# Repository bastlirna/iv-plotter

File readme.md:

# I·V Plotter 

_Tiny application for measurement of IV characteristics via DPS 5005 digital power supply._

## How it works

Some of [Rui Deng](https://rdtech.aliexpress.com) digital power supplies e.g. [DPS 5005](https://www.aliexpress.com/item/1000004290003.html) can be controled from PC via USB convertor. There is oficial app, but more importnat API documentation. So why not to use this API for something interesting that official app can not do...

### Resolution

DPS has resolution 10 mV for voltage and 1 mA for current. Also change of output is very slow and one must wait for settle down. 

This application is there for more demo or tool for explaining what is IV curve for newbes more then serious tool.

> Hovewer it can be used as example how to control DPS via API.

## How to use

```
git clone git@github.com:bastlirna/iv-plotter.git
cd app
npm install
npm start ttyUSB0
```

And enjoy...

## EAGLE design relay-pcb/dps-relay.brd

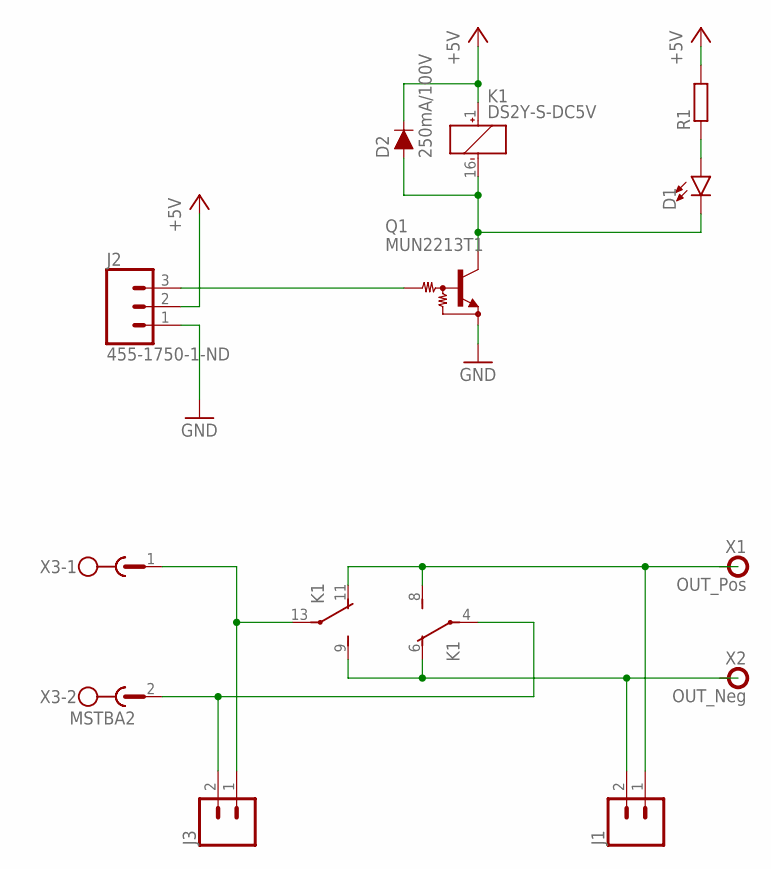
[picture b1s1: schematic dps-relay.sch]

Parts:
D1: LED3MM; LED_3MM
D2: 250mA/100V; SOD-323
J1, J3: CONN_02; 1X02
J2: 455-1750-1-ND; 1X03
K1: DS2Y-S-DC5V; DS2Y
Q1: MUN2213T1; SC59-BEC
R1: R-EU_R1206; R1206
X1: OUT_Pos; SOCKET_24.243
X2: OUT_Neg; SOCKET_24.243
X3: MSTBA2

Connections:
+5V: D2.C, J2.2, K1.1 (+), R1.2
GND: J2.1, Q1.E
IN_N: J3.1, K1.13, X3.1
IN_P: J3.2, K1.4, X3.2
unnamed: D1.A, R1.1
OUT_N: J1.1, K1.8 (S), K1.11 (O), X1.1, X1.2
OUT_P: J1.2, K1.6 (O), K1.9 (S), X2.1, X2.2
Q1_C: D1.K (C), D2.A, K1.16 (-), Q1.C
RIN: J2.3, Q1.B

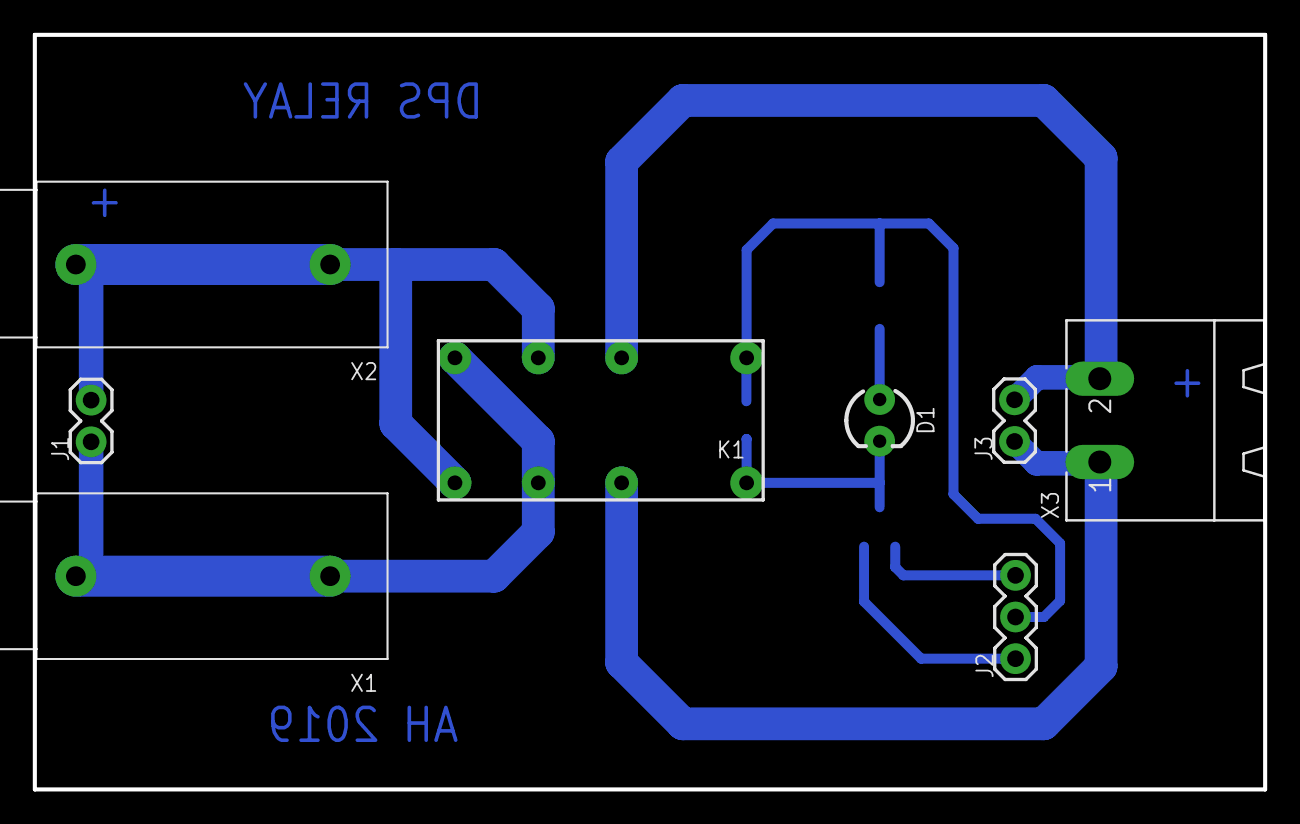
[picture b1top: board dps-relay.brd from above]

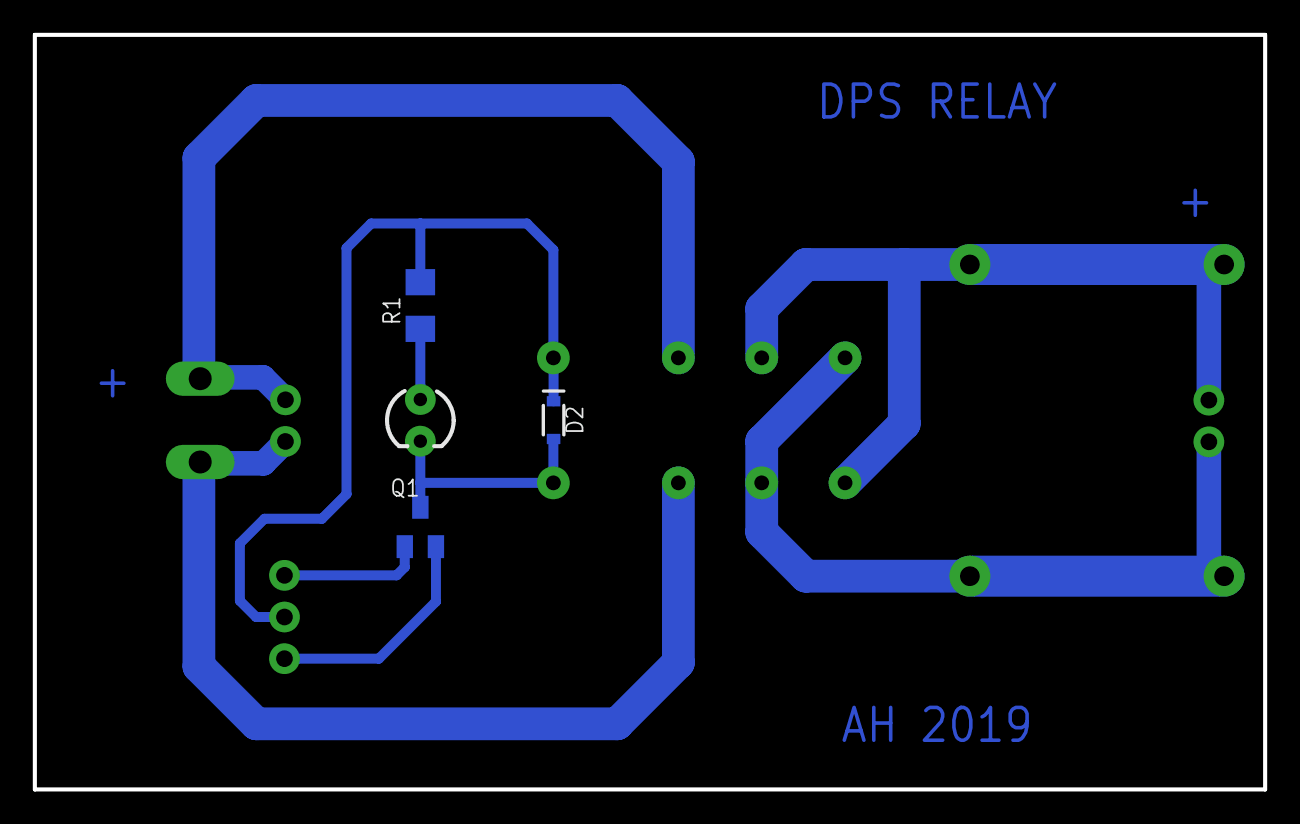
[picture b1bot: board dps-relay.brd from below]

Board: 2 copper layers, 75.0 x 46.0 mm, 11 parts (3 on the bottom side), 9 nets.

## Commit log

2019-09-16 Add init version of SW
2019-09-22 Add component box for 3D print
2019-09-22 Add relay pcb
2019-09-22 Add component list
2019-09-24 App improvement
2019-09-24 Chnage size of box
2019-10-02 Add 2 quadrant measurement
2019-10-02 Add boxes for LD
2019-10-02 Add screenshots
2019-10-02 Add readme
2019-10-02 Add diagram
2019-10-02 Add source of diagram
2019-10-02 Add communication port as argument
2019-10-02 Create LICENSE
2019-10-02 Chnage default values
2019-10-06 Fix typo
2020-07-18 Bump lodash from 4.17.15 to 4.17.19 in /app
    Bumps [lodash](https://github.com/lodash/lodash) from 4.17.15 to 4.17.19.
    - [Release notes](https://github.com/lodash/lodash/releases)
    - [Commits](https://github.com/lodash/lodash/compare/4.17.15...4.17.19)
2020-09-02 Bump bl from 3.0.0 to 3.0.1 in /app
    Bumps [bl](https://github.com/rvagg/bl) from 3.0.0 to 3.0.1.
    - [Release notes](https://github.com/rvagg/bl/releases)
    - [Commits](https://github.com/rvagg/bl/compare/v3.0.0...v3.0.1)
2021-05-10 Bump lodash from 4.17.15 to 4.17.21 in /app
    Bumps [lodash](https://github.com/lodash/lodash) from 4.17.15 to 4.17.21.
    - [Release notes](https://github.com/lodash/lodash/releases)
    - [Commits](https://github.com/lodash/lodash/compare/4.17.15...4.17.21)
2021-05-25 Bump browserslist from 4.7.0 to 4.16.6 in /app
    Bumps [browserslist](https://github.com/browserslist/browserslist) from 4.7.0 to 4.16.6.
    - [Release notes](https://github.com/browserslist/browserslist/releases)
    - [Changelog](https://github.com/browserslist/browserslist/blob/main/CHANGELOG.md)
    - [Commits](https://github.com/browserslist/browserslist/compare/4.7.0...4.16.6)
2021-05-29 Bump ws from 7.1.2 to 7.4.6 in /app
    Bumps [ws](https://github.com/websockets/ws) from 7.1.2 to 7.4.6.
    - [Release notes](https://github.com/websockets/ws/releases)
    - [Commits](https://github.com/websockets/ws/compare/7.1.2...7.4.6)
2021-08-11 Bump path-parse from 1.0.6 to 1.0.7 in /app
    Bumps [path-parse](https://github.com/jbgutierrez/path-parse) from 1.0.6 to 1.0.7.
    - [Release notes](https://github.com/jbgutierrez/path-parse/releases)
    - [Commits](https://github.com/jbgutierrez/path-parse/commits/v1.0.7)
    ---
    updated-dependencies:
    - dependency-name: path-parse
2022-02-10 Bump undefsafe from 2.0.2 to 2.0.5 in /app
    Bumps [undefsafe](https://github.com/remy/undefsafe) from 2.0.2 to 2.0.5.
    - [Release notes](https://github.com/remy/undefsafe/releases)
    - [Commits](https://github.com/remy/undefsafe/compare/v2.0.2...v2.0.5)
    ---
    updated-dependencies:
    - dependency-name: undefsafe
2022-12-04 Bump decode-uri-component from 0.2.0 to 0.2.2 in /app
    Bumps [decode-uri-component](https://github.com/SamVerschueren/decode-uri-component) from 0.2.0 to 0.2.2.
    - [Release notes](https://github.com/SamVerschueren/decode-uri-component/releases)
    - [Commits](https://github.com/SamVerschueren/decode-uri-component/compare/v0.2.0...v0.2.2)
    ---
    updated-dependencies:
    - dependency-name: decode-uri-component
2022-12-07 Bump qs and express in /app
    Bumps [qs](https://github.com/ljharb/qs) to 6.11.0 and updates ancestor dependency [express](https://github.com/expressjs/express). These dependencies need to be updated together.
    Updates `qs` from 6.7.0 to 6.11.0
    - [Release notes](https://github.com/ljharb/qs/releases)
    - [Changelog](https://github.com/ljharb/qs/blob/main/CHANGELOG.md)
    - [Commits](https://github.com/ljharb/qs/compare/v6.7.0...v6.11.0)
    Updates `express` from 4.17.1 to 4.18.2
2022-12-11 Bump express from 4.17.1 to 4.17.3 in /app
    Bumps [express](https://github.com/expressjs/express) from 4.17.1 to 4.17.3.
    - [Release notes](https://github.com/expressjs/express/releases)
    - [Changelog](https://github.com/expressjs/express/blob/master/History.md)
    - [Commits](https://github.com/expressjs/express/compare/4.17.1...4.17.3)
    ---
    updated-dependencies:
2023-01-04 Bump json5 from 2.1.0 to 2.2.3 in /app
    Bumps [json5](https://github.com/json5/json5) from 2.1.0 to 2.2.3.
    - [Release notes](https://github.com/json5/json5/releases)
    - [Changelog](https://github.com/json5/json5/blob/main/CHANGELOG.md)
    - [Commits](https://github.com/json5/json5/compare/v2.1.0...v2.2.3)
    ---
    updated-dependencies:

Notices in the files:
parts and their libraries:
SparkFun-Connectors: Licensing: Creative Commons ShareAlike 4.0 International - https://creativecommons.org/licenses/by-sa/4.0
